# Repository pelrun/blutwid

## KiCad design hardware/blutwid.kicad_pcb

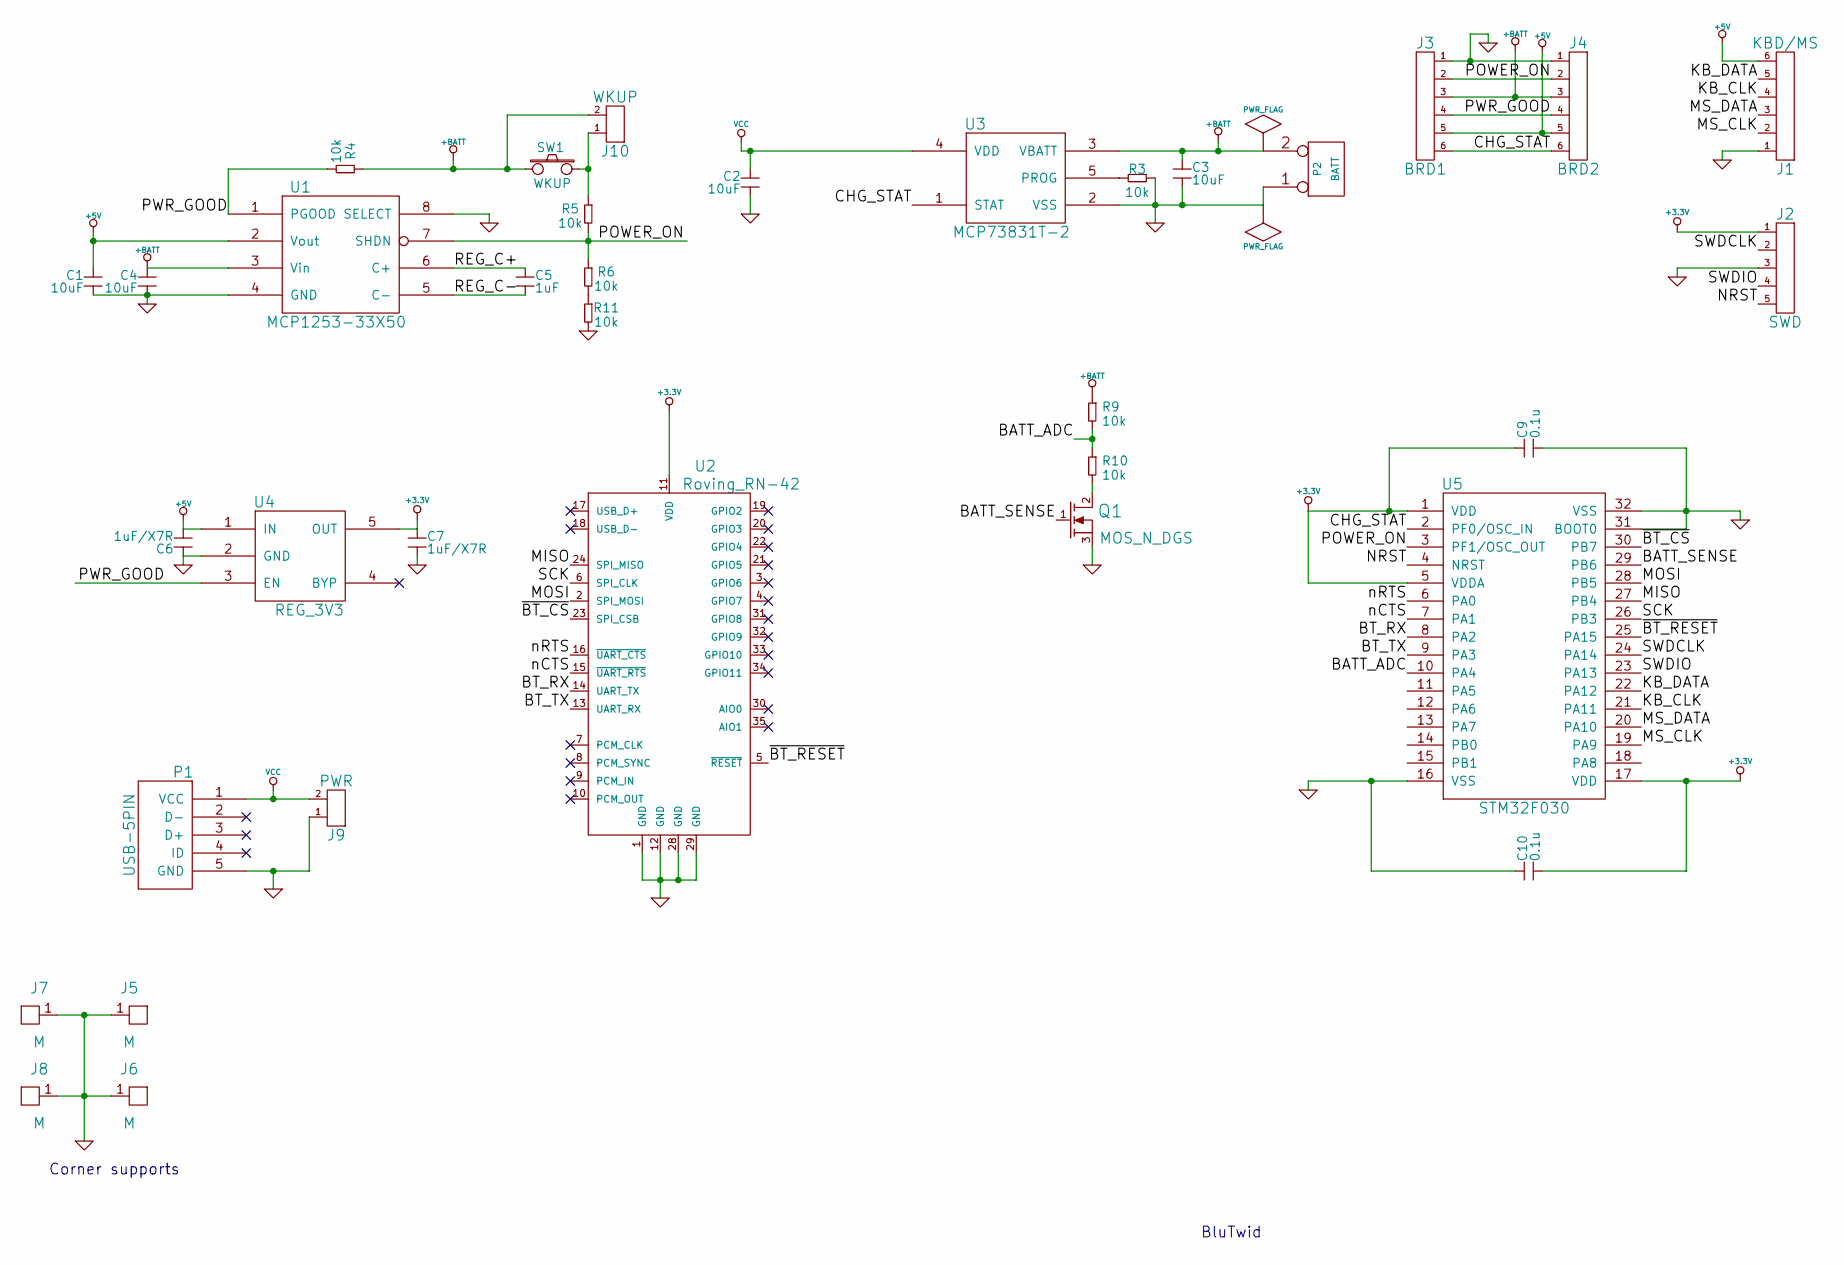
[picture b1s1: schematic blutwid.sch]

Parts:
C1, C2, C3, C4: 10uF; c_1206
C5: 1uF; c_0805
C6, C7: 1uF/X7R; c_0402
C9, C10: 0.1u; c_0402
J1: KBD/MS; pin_strip_6
J2: SWD; pin_strip_5
J3: BRD1; pin_strip_6
J4: BRD2; pin_strip_6
J5, J6, J7, J8: M; pin_strip_1
J9: PWR; pin_strip_2
J10: WKUP; pin_strip_2
P1: USB-5PIN; conn_usb_B_micro_smd-2
P2: BATT; pin_strip_2
Q1: MOS_N_DGS; sot23
R3, R4, R5, R6, R9, R10, R11: 10k; r_0402
SW1: WKUP; SW_SPST_EVQP7A
U1: MCP1253-33X50; msoic-8
U2: Roving_RN-42; w_rf_modules%3aroving_rn-42
U3: MCP73831T-2; sot23-5
U4: REG_3V3; sot23-5
U5: STM32F030; lqfp32

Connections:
+3.3V: C7.1, C9.1, C10.2, J2.1, U2.11 (VDD), U4.5 (OUT), U5.1 (VDD), U5.5 (VDDA), U5.17 (VDD)
+5V: C1.1, C6.2, J1.6, J3.5, J4.5, U1.2 (Vout), U4.1 (IN)
+BATT: C3.1, C4.1, J3.3, J4.3, J10.2, P2.2 (PM), R4.1, R9.1, SW1.2, U1.3 (Vin), U3.3 (VBATT)
/BATT_ADC: R9.2, R10.1, U5.10 (PA4)
/BATT_SENSE: Q1.1 (G), U5.29 (PB6)
/BT_RX: U2.14 (UART_TX), U5.8 (PA2)
/BT_TX: U2.13 (UART_RX), U5.9 (PA3)
/CHG_STAT: J3.6, J4.6, U3.1 (STAT), U5.2 (PF0/OSC_IN)
/KB_CLK: J1.4, U5.21 (PA11)
/KB_DATA: J1.5, U5.22 (PA12)
/MISO: U2.24 (SPI_MISO), U5.27 (PB4)
/MOSI: U2.2 (SPI_MOSI), U5.28 (PB5)
/MS_CLK: J1.2, U5.19 (PA9)
/MS_DATA: J1.3, U5.20 (PA10)
/NRST: J2.5, U5.4 (NRST)
/POWER_ON: J3.2, J4.2, R5.2, R6.1, U1.7 (SHDN), U5.3 (PF1/OSC_OUT)
/PWR_GOOD: J3.4, J4.4, R4.2, U1.1 (PGOOD), U4.3 (EN)
/REG_C+: C5.1, U1.6 (C+)
/REG_C-: C5.2, U1.5 (C-)
/SCK: U2.6 (SPI_CLK), U5.26 (PB3)
/SWDCLK: J2.2, U5.24 (PA14)
/SWDIO: J2.4, U5.23 (PA13)
/nCTS: U2.15 (~UART_RTS), U5.7 (PA1)
/nRTS: U2.16 (~UART_CTS), U5.6 (PA0)
/~BT_CS: U2.23 (SPI_CSB), U5.30 (PB7)
/~BT_RESET: U2.5 (~RESET), U5.25 (PA15)
GND: C1.2, C2.2, C3.2, C4.2, C6.1, C7.2, C9.2, C10.1, J1.1, J2.3, J3.1, J4.1, J5.1, J6.1, J7.1, J8.1, J9.1, P1.5 (GND), P2.1, Q1.3 (S), R3.2, R11.2, U1.4 (GND), U1.8 (SELECT), U2.1 (GND), U2.12 (GND), U2.28 (GND), U2.29 (GND), U3.2 (VSS), U4.2 (GND), U5.16 (VSS), U5.31 (BOOT0), U5.32 (VSS)
unnamed: J10.1, R5.1, SW1.1
unnamed: Q1.2 (D), R10.2
unnamed: R3.1, U3.5 (PROG)
unnamed: R6.2, R11.1
VCC: C2.1, J9.2, P1.1 (VCC), U3.4 (VDD)

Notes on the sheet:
BluTwid
Corner supports

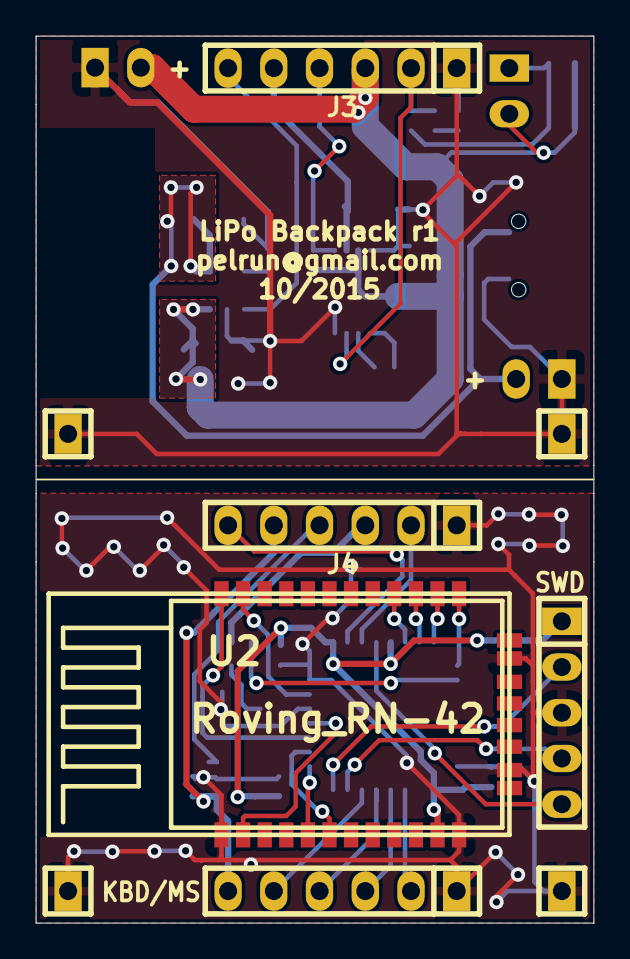
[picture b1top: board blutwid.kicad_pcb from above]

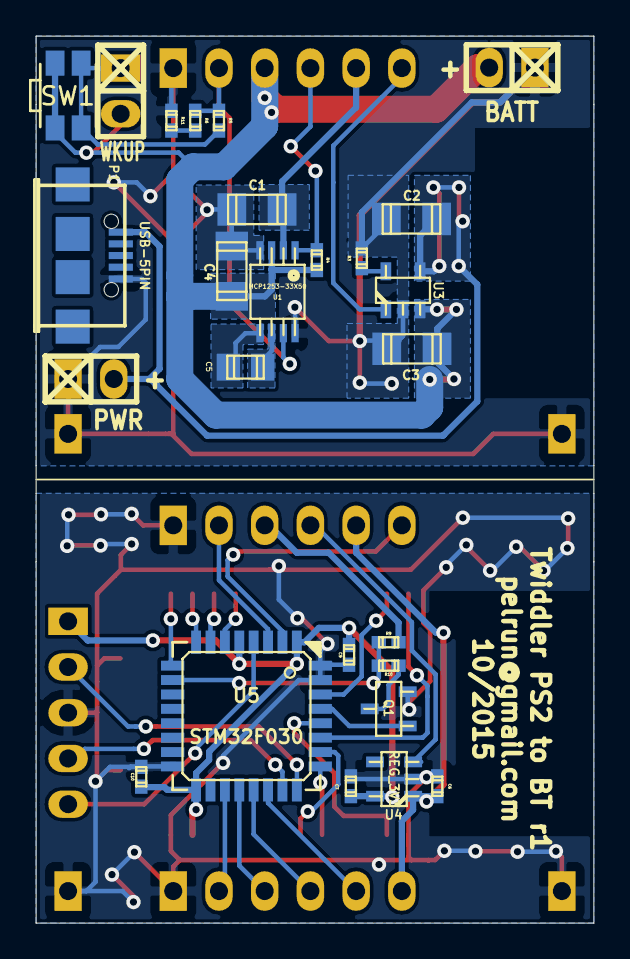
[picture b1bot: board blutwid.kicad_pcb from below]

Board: 2 copper layers, 31.0 x 49.3 mm, 36 parts (26 on the bottom side), 32 nets.

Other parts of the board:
SLOT: SLOT; MountingHole_2-5mm

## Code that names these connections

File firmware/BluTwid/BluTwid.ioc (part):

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Mcu.Name=STM32F030K6Tx
Mcu.Package=LQFP32
Mcu.UserName=STM32F030K6Tx
PA0.Mode=CTS_RTS
PA0.Signal=USART1_CTS
PA1.Mode=CTS_RTS
PA1.Signal=USART1_RTS
PA10.GPIOParameters=GPIO_PuPd,GPIO_Label,GPIO_ModeDefaultOutputPP
PA10.GPIO_Label=MS_DATA
PA10.GPIO_ModeDefaultOutputPP=GPIO_MODE_OUTPUT_OD
PA10.GPIO_PuPd=GPIO_PULLUP
PA10.Signal=GPIO_Output
PA11.GPIOParameters=GPIO_PuPd,GPIO_Label,GPIO_ModeDefaultOutputPP
PA11.GPIO_Label=KB_CLK
PA11.GPIO_ModeDefaultOutputPP=GPIO_MODE_OUTPUT_OD
PA11.GPIO_PuPd=GPIO_PULLUP
PA11.Signal=GPIO_Output
PA12.GPIOParameters=GPIO_PuPd,GPIO_Label,GPIO_ModeDefaultOutputPP
PA12.GPIO_Label=KB_DATA
PA12.GPIO_ModeDefaultOutputPP=GPIO_MODE_OUTPUT_OD
PA12.GPIO_PuPd=GPIO_PULLUP
PA12.Signal=GPIO_Output
PA13.Mode=Serial-WireDebug
PA13.Signal=SYS_SWDIO
PA14.Mode=Serial-WireDebug
PA14.Signal=SYS_SWCLK
PA15.GPIOParameters=GPIO_Label
PA15.GPIO_Label=BT_nRESET
PA15.Signal=GPIO_Output
PA2.GPIOParameters=GPIO_Label
PA2.GPIO_Label=BT_RX
PA2.Mode=Asynchronous
PA2.Signal=USART1_TX
PA3.GPIOParameters=GPIO_Label
PA3.GPIO_Label=BT_TX
PA3.Mode=Asynchronous
PA3.Signal=USART1_RX
PA4.GPIOParameters=GPIO_Label
PA4.GPIO_Label=BATT_ADC
PA4.Mode=IN4
PA4.Signal=ADC_IN4
PA9.GPIOParameters=GPIO_PuPd,GPIO_Label,GPIO_ModeDefaultOutputPP
PA9.GPIO_Label=MS_CLK
PA9.GPIO_ModeDefaultOutputPP=GPIO_MODE_OUTPUT_OD
PA9.GPIO_PuPd=GPIO_PULLUP
PA9.Signal=GPIO_Output
PB3.Mode=Full_Duplex_Master
PB3.Signal=SPI1_SCK
PB4.Mode=Full_Duplex_Master
PB4.Signal=SPI1_MISO
PB5.Mode=Full_Duplex_Master
PB5.Signal=SPI1_MOSI
PB6.GPIOParameters=GPIO_Label
PB6.GPIO_Label=BATT_SENSE
PB6.Signal=GPIO_Output
PB7.GPIOParameters=PinState,GPIO_Label
PB7.GPIO_Label=BT_nCS
PB7.PinState=GPIO_PIN_SET
PB7.Signal=GPIO_Output
PF0-OSC_IN.GPIOParameters=GPIO_Label
PF0-OSC_IN.GPIO_Label=CHG_STAT
PF0-OSC_IN.Signal=GPIO_Input
PF1-OSC_OUT.GPIOParameters=PinState,GPIO_Label
PF1-OSC_OUT.GPIO_Label=POWER_ON
PF1-OSC_OUT.PinState=GPIO_PIN_SET
PF1-OSC_OUT.Signal=GPIO_Output
RCC.SYSCLKFreq_VALUE=16000000
RCC.SYSCLKSource=RCC_SYSCLKSOURCE_PLLCLK
board=BluTwid

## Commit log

2016-05-05 Initial firmware commit
2016-05-05 Initial hardware commit, version r1
2017-04-14 Bunch of uncommitted code from last year.
2017-04-14 Add .gitignore
